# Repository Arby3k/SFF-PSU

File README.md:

# SFF-PSU
 A small form factor PSU

Hardware — contains the KiCAD Project, Schematics & Layout and Project Libraries

Firmware — contains any software developed for the Hardware

Docs — contains any data sheets or documentations

Production — contains the gerber files, BOM or anything required by the fabrication houses

Simulation — contains any simulation files and generated results

CAD — contains the 3D models and mechanical designs for enclosures or support

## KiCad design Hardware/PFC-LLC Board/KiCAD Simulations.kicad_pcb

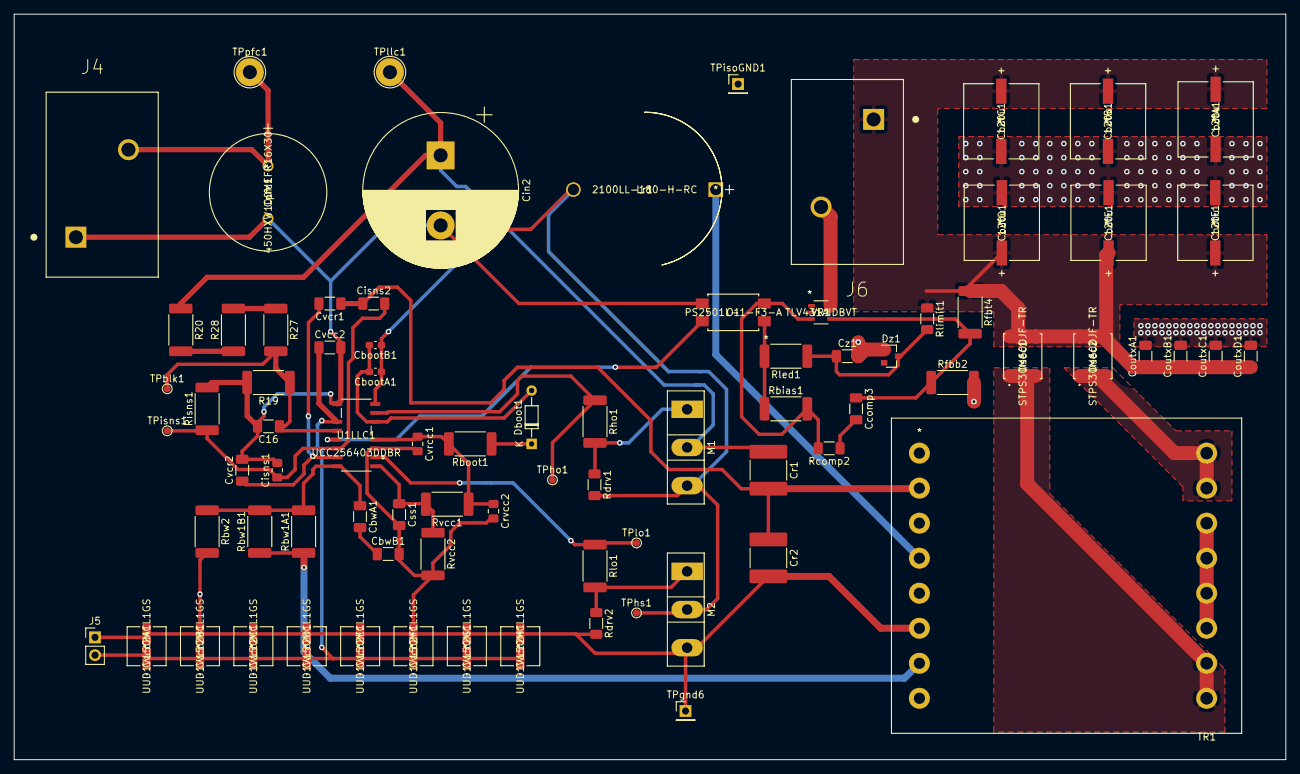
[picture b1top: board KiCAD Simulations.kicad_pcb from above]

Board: 2 copper layers, 181.5 x 106.4 mm, 81 parts (0 on the bottom side), 33 nets.

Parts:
C16: 220p; C_1206_3216Metric_Pad1.33x1.80mm_HandSolder
CbootA1: 470n; C_0603_1608Metric_Pad1.08x0.95mm_HandSolder
CbootB1: 470n; C_0603_1608Metric_Pad1.08x0.95mm_HandSolder
CbwA1: 12p; C_1206_3216Metric_Pad1.33x1.80mm_HandSolder
CbwB1: 12p; C_1206_3216Metric_Pad1.33x1.80mm_HandSolder
Ccomp3: 2.7n; C_1206_3216Metric_Pad1.33x1.80mm_HandSolder
Cin2: 47u; CP_Radial_D22.0mm_P10.00mm_SnapIn
Cisns1: 3.3p; C_0805_2012Metric_Pad1.18x1.45mm_HandSolder
Cisns2: 220p; C_1206_3216Metric_Pad1.33x1.80mm_HandSolder
CoutA1: 120u; 35SVPF120M
CoutB1: 120u; 35SVPF120M
CoutC1: 120u; 35SVPF120M
CoutD1: 120u; 35SVPF120M
CoutE1: 120u; 35SVPF120M
CoutF1: 120u; 35SVPF120M
CoutxA1: 22u; C_1206_3216Metric_Pad1.33x1.80mm_HandSolder
CoutxB1: 22u; C_1206_3216Metric_Pad1.33x1.80mm_HandSolder
CoutxC1: 22u; C_1206_3216Metric_Pad1.33x1.80mm_HandSolder
CoutxD1: 22u; C_1206_3216Metric_Pad1.33x1.80mm_HandSolder
Cpfc1: 450HXW100MEFR16X30
Cr1, Cr2: 150n; C_2220_5650Metric_Pad1.97x5.40mm_HandSolder
Crvcc2: 4.7u; C_0805_2012Metric_Pad1.18x1.45mm_HandSolder
Css1: 150n; C_1206_3216Metric_Pad1.33x1.80mm_HandSolder
Cvcc2: 2.2u; C_1206_3216Metric_Pad1.33x1.80mm_HandSolder
Cvcc2A1, Cvcc2B1, Cvcc2C1, Cvcc2D1, Cvcc2E1, Cvcc2F1, Cvcc2G1, Cvcc2H1: UUD1V150MCL1GS
Cvcr1: 220p; C_1206_3216Metric_Pad1.33x1.80mm_HandSolder
Cvcr2: 22n; C_1206_3216Metric_Pad1.33x1.80mm_HandSolder
Cvrcc1: 4.7u; C_0805_2012Metric_Pad1.18x1.45mm_HandSolder
Cz1: 100n; C_1206_3216Metric_Pad1.33x1.80mm_HandSolder
Dboot1: DIODE; D_DO-34_SOD68_P7.62mm_Horizontal
Dsec1, Dsec2: STPS30M60DJF-TR; STPS30M60DJF-TR-Modified
Dz1: BZX84Cxx; D_SOT-23_ANK
J4, J6: 1792229; PHOENIX_1792229
J5: Conn_01x02_Female; PinHeader_1x02_P2.54mm_Vertical
Lr1: 2100LL-180-H-RC
M1, M2: IPP060N06N; TO-247-3_Vertical
O1: PS2501L-1-F3-A
R19: 2.7k; R_2512_6332Metric_Pad1.40x3.35mm_HandSolder
R20, R27: 120k; R_2512_6332Metric_Pad1.40x3.35mm_HandSolder
R28: 100k; R_2512_6332Metric_Pad1.40x3.35mm_HandSolder
Rbias1: 6.04k; R_2512_6332Metric_Pad1.40x3.35mm_HandSolder
Rboot1: 2.20; R_2512_6332Metric_Pad1.40x3.35mm_HandSolder
Rbw1A1, Rbw1B1: 82k; R_2512_6332Metric_Pad1.40x3.35mm_HandSolder
Rbw2: 10k; R_2512_6332Metric_Pad1.40x3.35mm_HandSolder
Rcomp2: 18.7k; R_1206_3216Metric_Pad1.30x1.75mm_HandSolder
Rdrv1, Rdrv2: 5.11k; R_1206_3216Metric_Pad1.30x1.75mm_HandSolder
Rfbb2: 8.06k; R_2512_6332Metric_Pad1.40x3.35mm_HandSolder
Rfbt4: 110k; R_2512_6332Metric_Pad1.40x3.35mm_HandSolder
Rho1: 1; R_2512_6332Metric_Pad1.40x3.35mm_HandSolder
Risns1: 390; R_2512_6332Metric_Pad1.40x3.35mm_HandSolder
Rled1: 36.5k; R_2512_6332Metric_Pad1.40x3.35mm_HandSolder
Rlimit1: 18.2k; R_1206_3216Metric_Pad1.30x1.75mm_HandSolder
Rlo1: 1; R_2512_6332Metric_Pad1.40x3.35mm_HandSolder
Rvcc1: 220k; R_2512_6332Metric_Pad1.40x3.35mm_HandSolder
Rvcc2: 1.2M; R_2512_6332Metric_Pad1.40x3.35mm_HandSolder
TPblk1: TestPoint; TestPoint_Pad_D1.0mm
TPgnd6: TestPoint; PinHeader_1x01_P2.54mm_Vertical
TPho1: TestPoint; TestPoint_Pad_D1.0mm
TPhs1: TestPoint; TestPoint_Pad_D1.0mm
TPisns1: TestPoint; TestPoint_Pad_D1.0mm
TPisoGND1: TestPoint; PinHeader_1x01_P2.54mm_Vertical
TPllc1: TestPoint; TestPoint_THTPad_D4.0mm_Drill2.0mm
TPlo1: TestPoint; TestPoint_Pad_D1.0mm
TPpfc1: TestPoint; TestPoint_THTPad_D4.0mm_Drill2.0mm
TR1: TRANSF6-WE; Transformer
U1LLC1: UCC256403DDBR
VR1: TLV431AIDBVT

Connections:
/LLC/BLK: C16.1, R19.1, R27.2, TPblk1.1, U1LLC1.4
/LLC/HO: Rho1.1, TPho1.1, U1LLC1.15
/LLC/HS: CbootA1.1, CbootB1.1, Lr1.2, M1.3, M2.2, Rdrv1.2, TPhs1.1, U1LLC1.16
/LLC/LO: Rlo1.1, TPlo1.1, U1LLC1.10
GND: C16.2, CbwB1.2, Cin2.2, Cisns1.2, Cpfc1.2, Cr2.2, Crvcc2.2, Css1.2, Cvcc2.2, Cvcc2A1.2, Cvcc2B1.2, Cvcc2C1.2, Cvcc2D1.2, Cvcc2E1.2, Cvcc2F1.2, Cvcc2G1.2, Cvcc2H1.2, Cvcr2.2, Cvrcc1.2, J4.1, J5.1, M2.3, O1.3, R19.2, Rbw2.2, Rdrv2.2, Risns1.2, Rvcc2.2, TPgnd6.1, TR1.6, U1LLC1.1, U1LLC1.11
GND1: CoutA1.2, CoutB1.2, CoutC1.2, CoutD1.2, CoutE1.2, CoutF1.2, CoutxA1.2, CoutxB1.2, CoutxC1.2, CoutxD1.2, Cz1.2, Dz1.2, J6.2, Rfbb2.2, TPisoGND1.1, TR1.11, TR1.12, TR1.13, TR1.14, VR1.5
unnamed: CbootA1.2, CbootB1.2, Dboot1.2, U1LLC1.14
unnamed: CbwA1.1, Rbw1A1.2, Rbw1B1.2, Rbw2.1, U1LLC1.8
unnamed: CbwA1.2, CbwB1.1
unnamed: Ccomp3.1, Rfbb2.1, Rfbt4.2, VR1.4
unnamed: Ccomp3.2, Rcomp2.1
unnamed: Cin2.1, Cr1.1, M1.2, R20.1, TPllc1.1
unnamed: Cisns1.1, Cisns2.2, Risns1.1, TPisns1.1, U1LLC1.6
unnamed: Cisns2.1, Cr1.2, Cr2.1, Cvcr1.1, TR1.2
unnamed: CoutA1.1, CoutB1.1, CoutC1.1, CoutD1.1, CoutE1.1, CoutF1.1, CoutxA1.1, CoutxB1.1, CoutxC1.1, CoutxD1.1, Dsec1.5, Dsec1.6, Dsec1.7, Dsec1.8, Dsec2.5, Dsec2.6, Dsec2.7, Dsec2.8, J6.1, Rfbt4.1, Rlimit1.1
unnamed: Cpfc1.1, J4.2, TPpfc1.1
unnamed: Crvcc2.1, Cvrcc1.1, Rboot1.2, Rvcc1.1, U1LLC1.12
unnamed: Css1.1, Rvcc1.2, Rvcc2.1, U1LLC1.9
unnamed: Cvcc2.1, Cvcc2A1.1, Cvcc2B1.1, Cvcc2C1.1, Cvcc2D1.1, Cvcc2E1.1, Cvcc2F1.1, Cvcc2G1.1, Cvcc2H1.1, J5.2, U1LLC1.3
unnamed: Cvcr1.2, Cvcr2.1, U1LLC1.7
unnamed: Cz1.1, Dz1.1, Rled1.1, Rlimit1.2
unnamed: Dboot1.1, Rboot1.1
unnamed: Dsec1.1, Dsec1.2, Dsec1.3, Dsec1.4, TR1.9, TR1.10
unnamed: Dsec2.1, Dsec2.2, Dsec2.3, Dsec2.4, TR1.15, TR1.16
unnamed: Lr1.1, TR1.4
unnamed: M1.1, Rdrv1.1, Rho1.2
unnamed: M2.1, Rdrv2.1, Rlo1.2
unnamed: O1.1, Rbias1.1, Rled1.2
unnamed: O1.2, Rbias1.2, Rcomp2.2, VR1.3
unnamed: O1.4, U1LLC1.5
unnamed: R20.2, R28.1
unnamed: R27.1, R28.2
unnamed: Rbw1A1.1, Rbw1B1.1, TR1.7

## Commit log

2021-02-11 Added 402 SMD Resistor
2021-02-11 added hi
2021-02-11 Required Resistors added to Library
2021-02-11 Added Capacitors
2021-02-11 More Parts added
2021-02-11 .DS_Store File removed from Git
2021-02-11 Added radial can capacitors
2021-02-11 More Parts
2021-02-11 Dboost Diode
2021-02-11 KiCAD Thing
2021-02-11 fixing DS_Store issue
2021-02-11 DS_store gitnore fixed
2021-02-12 Added new ICs to library
2021-02-12 LLC WIP
2021-02-12 Updated LLC schematic
2021-02-20 Start of PCB
2021-02-24 Schematic/PCB updates
    Minor updates to schematic and some place of PCB components as been done
2021-02-25 Added transformer footprint
2021-02-26 All footprints except PFC output caps
2021-03-03 missing 4 PFC components
2021-03-04 All component footprints found and ready for PCB layout
2021-03-04 initial layout
2021-03-05 layout done with some routing for LLC
2021-03-05 More progress on routing PCB
2021-03-06 LLC routed (trace sizing not done)
2021-03-06 Routing complete (except trace widths)
2021-03-07 PCB with flooding (expect GND)
2021-03-08 Gerber files generated
2021-03-12 Added Test points
    Added Test points
    Changed Capacitor Values around
2021-03-12 PFC footprints updated
2021-03-12 new PFC Board/Design
2021-03-15 PFC Gerber files generated
2021-03-15 Gerber files regenerated
2021-03-23 LLC footprints and schematic update
    No transformer yet
2021-03-30 LLC PCB ready w/ PFC board
2021-03-30 LLC gerber files generated
2021-03-30 LLC gerber files regenerated
    2512 footprints updated to 1206 for Rlimit, Rcomp, drv1, drv2

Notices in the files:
parts and their libraries:
Copyright 2016 Accelerated Designs. All rights reserved.
